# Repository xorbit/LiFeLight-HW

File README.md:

LiFeLight hardware
==================

[LiFePO4wered/USB]: http://lifepo4wered.com
[MSP430G2210]: http://www.ti.com/product/msp430g2210
[CCS]: http://www.ti.com/tool/ccstudio
[Github project]: https://github.com/xorbit/LiFeLight
[OSH Park]: https://oshpark.com/shared_projects/UGFRTknj

This is the Eagle source project for the LiFeLight demo board hardware.  LiFeLight is a board developed as a soldering kit for the Maker Faire, that can be added to a [LiFePO4wered/USB][] module to create a programmable touch flashlight.  It's a good example of getting decent functionality with minimal, low cost hardware.  It has the following subsystems:

Touch sensor
------------

The touch sensor is a simple PCB pad.  All touch detection functionality is implemented in software, using a simple interrupt driven charge/discharge scheme.

LED booster
-----------

To have high light output using various colors of LED (including white), using a supply voltage that can be as low as 2V, a simple booster circuit was implemented.  The software drives the LED output at ~100kHz.  Yes, the LED has to be mounted "backwards", because it is powered from the inductor's flyback voltage.

Microcontroller
---------------

All LiFeLight functionality is implemented in software that runs on a low cost [MSP430G2210][] microcontroller.  The software was implemented using [CCS][].  The source code can be found in this [Github project][].

Ordering
--------

If you don't want to deal with doing it yourself, the PCBs can be ordered conveniently from [OSH Park][].

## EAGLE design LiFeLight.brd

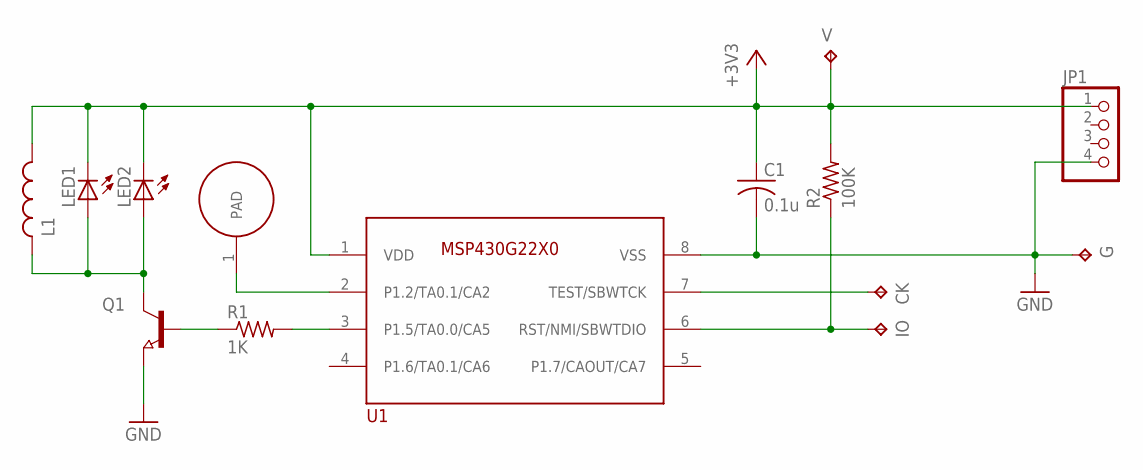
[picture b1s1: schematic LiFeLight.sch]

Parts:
C1: 0.1u; C0805K
CK: TPB1,27; B1,27
G: TPB1,27; B1,27
IO: TPB1,27; B1,27
JP1: PINHD-1X4; 1X04
L1: L-USL2825P; L2825P
LED1: LEDSQR2X5; LED2X5
LED2: LEDSMT1206; 1206
Q1: NPN-TRANSISTOR_SOT23; SOT23
R1: 1K; R0805
R2: 100K; R0805
TOUCH1: TOUCHPAD8MM; TOUCHPAD8
U1: MSP430G22X0; SO08
V: TPB1,27; B1,27

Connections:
+3V3: C1.1, JP1.1, L1.1, LED1.K (C), LED2.C, R2.2, U1.1 (VDD), V.TP
GND: C1.2, G.TP, JP1.4, Q1.2 (E), U1.8 (VSS)
unnamed: L1.2, LED1.A, LED2.A, Q1.3 (C)
unnamed: IO.TP, R2.1, U1.6 (RST/NMI/SBWTDIO)
unnamed: CK.TP, U1.7 (TEST/SBWTCK)
unnamed: Q1.1 (B), R1.1
unnamed: TOUCH1.1, U1.2 (P1.2/TA0.1/CA2)
unnamed: R1.2, U1.3 (P1.5/TA0.0/CA5)

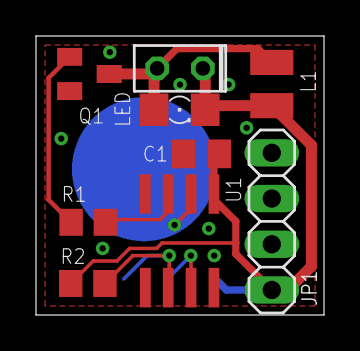
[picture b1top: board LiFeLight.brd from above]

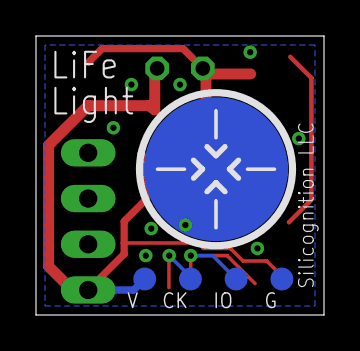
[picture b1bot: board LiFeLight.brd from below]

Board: 2 copper layers, 16.0 x 15.5 mm, 14 parts (5 on the bottom side), 8 nets.

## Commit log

2015-01-30 Add OSH Park ordering link
2015-09-11 Add schematic PDF
